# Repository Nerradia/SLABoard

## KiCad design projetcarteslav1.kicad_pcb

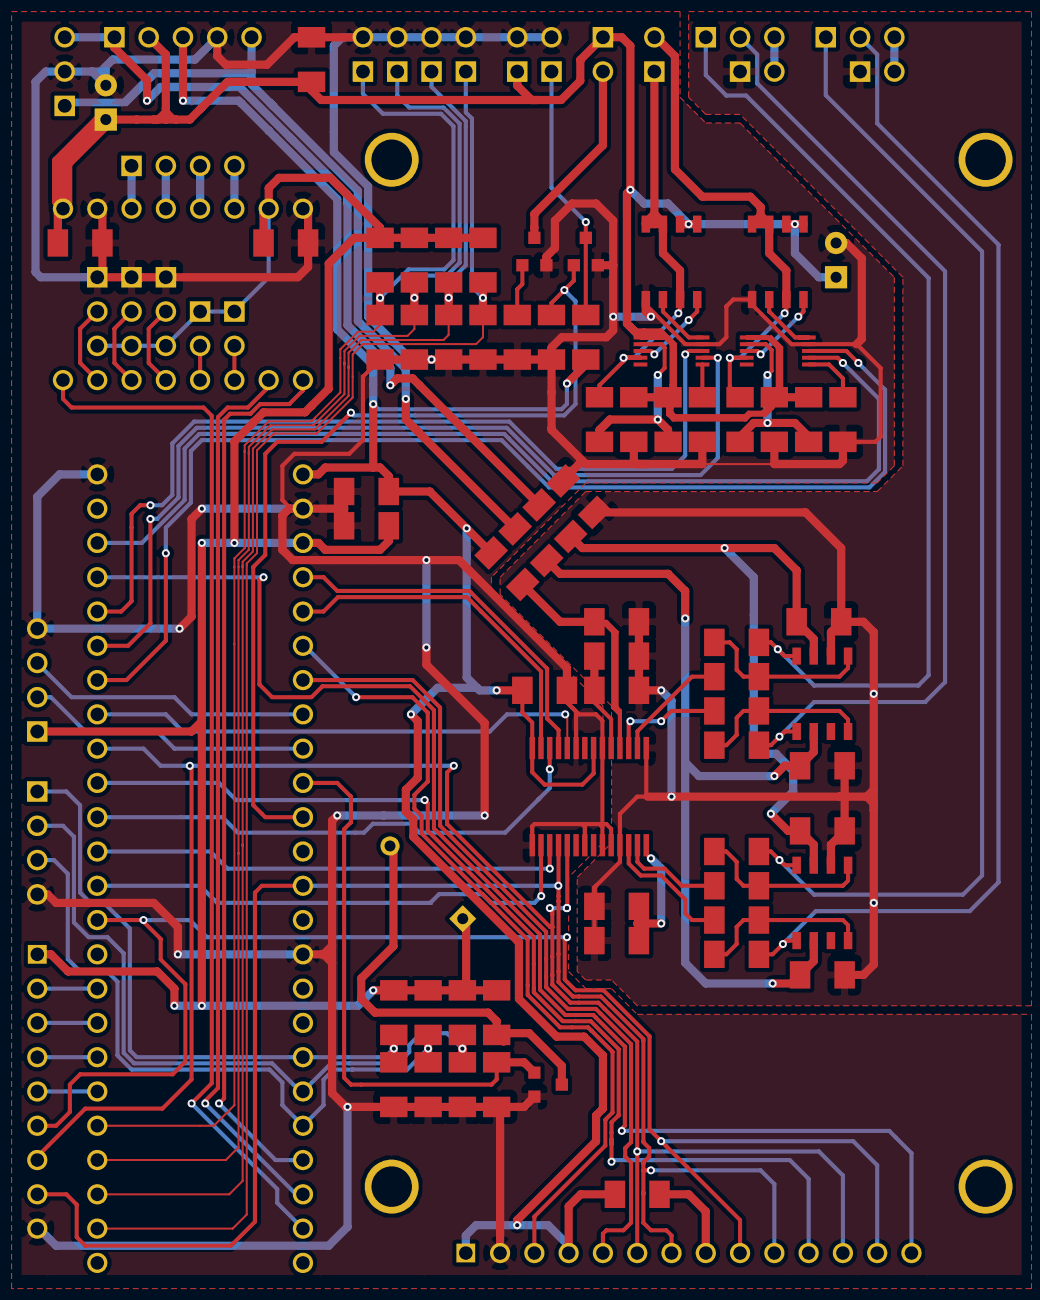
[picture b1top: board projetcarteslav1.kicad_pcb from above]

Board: 2 copper layers, 95 parts (0 on the bottom side), 85 nets.

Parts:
C1, C2, C3, C7, C8, C9, C10, C11, C12, C13, C14, C15, C16, C22, C23, C24, C25, C26, C27, C28: 220n; SM1206
C4, C17: 220u; C1V7H
C5, C6, C18, C20: 10u; SM1206
C19, C21: 100n; SM1206
D1, D2: DIODE; SM1206POLINV
JP1, JP2, JP3: JUMPER3; PIN_ARRAY_3X1
JP4, JP5, JP6, JP7: JUMPER; PIN_ARRAY_2X1
K1: Galvo X; PIN_ARRAY_3X1
K2: Galvo Y; PIN_ARRAY_3X1
K3: Galvo pwr; PIN_ARRAY_3X1
L1, L2, L3, L4: INDUCTOR; SM1206
P1: I2C; PIN_ARRAY_4x1
P2: SCREEN; Ecran
P3: SPI; SIL-9
P4: MOT_A; PIN_ARRAY_2X1
P5: LASER_~EN; PIN_ARRAY_2X1
P6: MOT_Z; PIN_ARRAY_4x1
P7: ALIM; PIN_ARRAY_5x1
P8: SW_ZMIN; PIN_ARRAY_2X1
P9: SW_ZMAX; PIN_ARRAY_2X1
P10: SW_AMIN; PIN_ARRAY_2X1
P11: SW_AMAX; PIN_ARRAY_2X1
P12: ROT_ENC; PIN_ARRAY_4x1
P13: FAN; PIN_ARRAY_2X1
P14: Laser pwr; PIN_ARRAY_2X1
Q1, Q2: FDS6898A; so-8
Q3, Q4, Q5: DMG3420U; SOT23GDS
R1, R3, R4, R5, R10, R24, R25, R26, R32: 10k; SM1206
R2: 100; SM1206
R6, R7, R8, R9: 374; SM1206
R11, R12, R13, R14: 750; SM1206
R15, R16, R18, R20, R22: 1k; SM1206
SP1: SPEAKER; BUZ3-5
U1: TEENSY3.6; Teensy3.6
U2, U3: LM5106; msoic-10
U6: AD1852; ssop-28
U7: TMC2100
U8, U9: OPA1632; so-8
svg2mod-rev: G***; svg2mod-rev

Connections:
+3.3V: C10.1, C11.1, JP1.3, JP2.3, JP3.3, JP4.1, JP5.1, P1.1, P3.1, R15.1, R16.1, R18.1, R20.1, R22.1, R24.1, R25.1, R26.1, SP1.1, U1.3V1, U7.10
+5VA: C16.1, L4.1, U6.18
+5VD: C7.1, C8.1, L4.2, P2.1, P2.4, P7.3, R2.2, R5.1, U1.Vin, U6.21, U6.28
+12V: C2.1, C3.1, C4.1, C5.1, C6.1, C17.1, D1.1, D2.1, P7.2, P13.1, P14.1, Q1.5, Q1.6, Q2.5, Q2.6, U2.1, U3.1, U7.16
+15V: C12.1, C13.1, L2.1, U8.3, U9.3
-15V: C14.1, C15.1, L3.1, U8.6, U9.6
/BP: C28.1, P12.3, R26.2, U1.37
/DAC_RESET: U1.6, U6.24
/DRV_DIR: U1.36, U7.8
/DRV_EN: U1.34, U7.1
/DRV_STEP: U1.35, U7.7
/FAN_PWM: Q3.G, R32.1
/I2C_SCL: P1.3, U1.19
/I2C_SDA: P1.2, U1.18
/I2S_BCLK: U1.9, U6.26
/I2S_L/~R~CLK: U1.23, U6.25
/I2S_MCLK: U1.11, U6.2
/I2S_SDATA: U1.22, U6.27
/LASER_EN: Q4.G, R4.1, U1.16
/PH_ENA: U1.4, U2.7
/PH_ENB: U1.1, U3.7
/PH_INA: U1.3, U2.8
/PH_INB: U1.5, U3.8
/R+: C26.1, P12.1, R24.2, U1.39
/R-: C27.1, P12.2, R25.2, U1.38
/SCREEN_D/C: P2.5, U1.20
/SPEAKER: Q5.G, R10.1, U1.17
/SPI_CLK: P2.7, P2.10, P3.8, U1.14, U6.4
/SPI_CS_DAC: U1.10, U6.3
/SPI_CS_EXT1: P3.5, U1.27
/SPI_CS_EXT2: P3.4, U1.26
/SPI_CS_EXT3: P3.3, U1.25
/SPI_CS_EXT4: P3.2, U1.24
/SPI_CS_SCREEN: P2.3, U1.21
/SPI_CS_TOUCH: P2.11, U1.8
/SPI_MISO: P2.9, P2.13, P3.6, U1.12
/SPI_MOSI: P2.6, P2.12, P3.7, U1.7, U6.5
/SW1: C22.1, P8.1, R16.2, U1.31
/SW2: C23.1, P9.1, R18.2, U1.30
/SW3: C24.1, P10.1, R20.2, U1.29
/SW4: C25.1, P11.1, R22.2, U1.28
/T_IRQ: P2.14, U1.2
AGND: C12.2, C13.2, C14.2, C15.2, C16.2, C18.2, C19.2, C20.2, C21.2, JP6.1, JP7.1, L1.2, U6.11, U6.15, U8.2, U9.2
GND: C2.2, C3.2, C4.2, C5.2, C6.2, C7.2, C8.2, C10.2, C11.2, C17.2, C22.2, C23.2, C24.2, C25.2, C26.2, C27.2, C28.2, JP1.1, JP2.1, JP3.1, K3.2, L1.1, P1.4, P2.2, P3.9, P5.2, P7.4, P8.2, P9.2, P10.2, P11.2, P12.4, P14.2, Q1.1, Q2.1, Q3.S, Q4.S, Q5.S, R1.2, R3.2, R4.2, R10.2, R32.2, U1.AGND, U1.GND1, U1.GND2, U2.9, U3.9, U6.1, U6.7, U6.9, U6.10, U6.20, U6.23, U7.9, U7.15
unnamed: K3.3, L2.2, P7.1
unnamed: P5.1, Q4.D, R5.2
unnamed: R7.1, U6.17
unnamed: R8.1, U6.13
unnamed: K1.1, R11.2, U8.4
unnamed: R6.2, R11.1, U8.1
unnamed: C18.1, C19.1, U6.19
unnamed: R9.1, U6.12
unnamed: K2.2, R14.2, U9.5
unnamed: R9.2, R14.1, U9.8
unnamed: R6.1, U6.16
unnamed: R8.2, R13.1, U9.1
unnamed: K2.1, R13.2, U9.4
unnamed: R7.2, R12.1, U8.8
unnamed: JP7.2, K2.3
unnamed: Q5.D, R15.2, SP1.2
unnamed: C20.1, C21.1, U6.14
unnamed: K1.2, R12.2, U8.5
unnamed: JP6.2, K1.3
unnamed: P13.2, Q3.D
unnamed: K3.1, L3.2, P7.5
unnamed: P2.8, R2.1
unnamed: P6.1, U7.14
unnamed: Q1.4, U2.3
unnamed: C1.1, D1.2, U2.2
unnamed: Q1.2, U2.10
unnamed: JP1.2, U7.2
unnamed: JP2.2, U7.3
unnamed: JP3.2, U7.4
unnamed: JP4.2, U7.5
unnamed: JP5.2, U7.6
unnamed: P6.4, U7.11
unnamed: P6.3, U7.12
unnamed: P6.2, U7.13
unnamed: C1.2, P4.1, Q1.3, Q1.7, Q1.8, U2.4
unnamed: C9.2, P4.2, Q2.3, Q2.7, Q2.8, U3.4
unnamed: R1.1, U2.6
unnamed: C9.1, D2.2, U3.2
unnamed: R3.1, U3.6
unnamed: Q2.2, U3.10
unnamed: Q2.4, U3.3

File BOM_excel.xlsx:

Généré par KiCad |  |  |  | RS
Valeur | Nombre | Références |  | Prix TTC pièce | Quantité par paquet | Référence RS
100n | 2 | C19 C21
220n | 20 | C1 C2 C3 C7 C8 C9 C10 C11 C12 C13 C14 C15 C16 C22 C23 C24 C25 C26 C27 C28
10u | 4 | C5 C6 C18 C20
220u | 2 | C4 C17
DIODE | 2 | D1 D2
JUMPER3 | 3 | JP1 JP2 JP3
JUMPER | 4 | JP4 JP5 JP6 JP7
Galvo X | 1 | K1
Galvo Y | 1 | K2
Galvo pwr | 1 | K3
INDUCTOR | 4 | L1 L2 L3 L4
I2C | 1 | P1
SCREEN | 1 | P2
SPI | 1 | P3
MOT_A | 1 | P4
LASER_~EN | 1 | P5
MOT_Z | 1 | P6
ALIM | 1 | P7
SW_ZMIN | 1 | P8
SW_ZMAX | 1 | P9
SW_AMIN | 1 | P10
SW_AMAX | 1 | P11
ROT_ENC | 1 | P12
FAN | 1 | P13
Laser pwr | 1 | P14
FDS6898A | 2 | Q1 Q2
DMG3420U | 3 | Q3 Q4 Q5
100 | 1 | R2
374 | 4 | R6 R7 R8 R9
750 | 4 | R11 R12 R13 R14
1k | 5 | R15 R16 R18 R20 R22
10k | 9 | R1 R3 R4 R5 R10 R24 R25 R26 R32
SPEAKER | 1 | SP1
TEENSY3.6 | 1 | U1
LM5106 | 2 | U2 U3 |  | 1.76 | 5 | 651-2789
AD1852 | 1 | U6 |  | 15.47 | 1 | 709-5614
TMC2100 | 1 | U7
OPA1632 | 2 | U8 U9 |  | 6.48 | 1 | 619-9875

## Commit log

2017-08-12 Fixed C5 silkscreen, fixed shorts of speaker terminals.
2017-09-08 Creation of BOM
2017-09-09 progress on BOM
2017-09-21 received components
